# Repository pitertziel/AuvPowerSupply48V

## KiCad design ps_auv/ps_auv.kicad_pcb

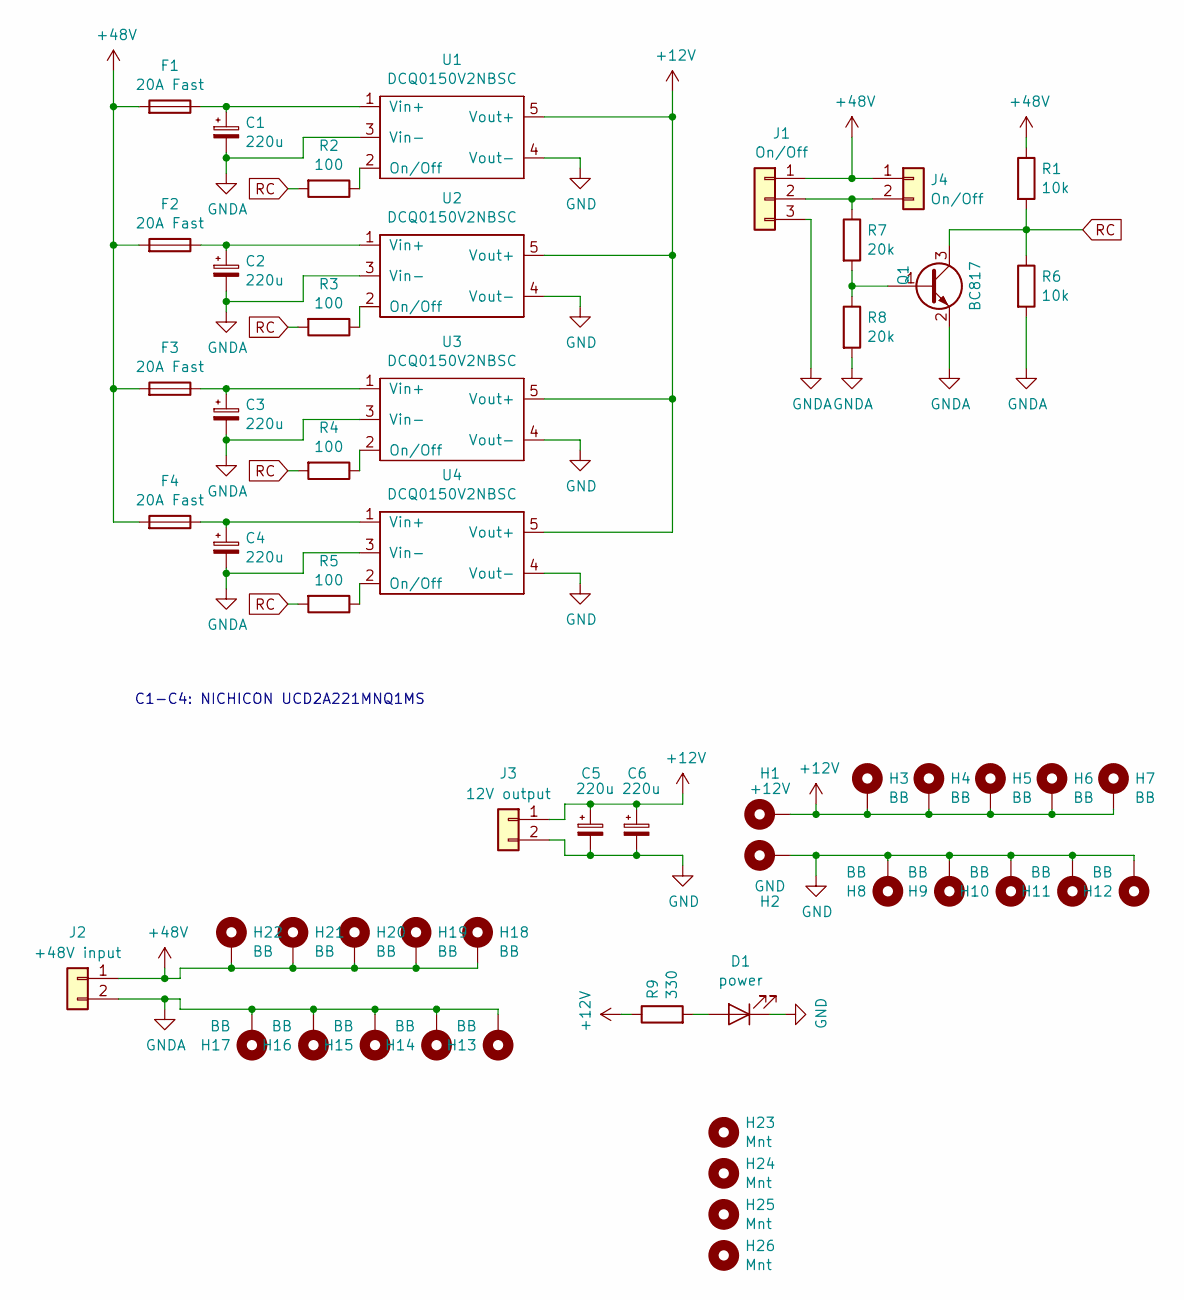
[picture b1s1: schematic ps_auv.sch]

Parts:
C1, C2, C3, C4: 220u; CP_Elec_18x17.5
C5, C6: 220u; CP_EIA-7343-43_Kemet-X
D1: power; LED_0805_2012Metric
F1, F2, F3, F4: 20A Fast; Fuseholder_Blade_Mini_Keystone_3568
H1: +12V; MountingHole_6.4mm_M6_Pad
H2: GND; MountingHole_6.4mm_M6_Pad
H3, H4, H5, H6, H7, H8, H9, H10, H11, H12, H13, H14, H15, H16, H17, H18, H19, H20, H21, H22: BB; MountingHole_2.2mm_M2_Pad
H23, H24, H25, H26: Mnt; MountingHole_2.2mm_M2
J1: On/Off; Molex_SPOX_5268-03A_1x03_P2.50mm_Horizontal
J2: +48V input
J3: 12V output
J4: On/Off; Molex_SPOX_5268-02A_1x02_P2.50mm_Horizontal
Q1: BC817; SOT-23
R1, R6: 10k; R_0805_2012Metric
R2, R3, R4, R5: 100; R_0805_2012Metric
R7, R8: 20k; R_0805_2012Metric
R9: 330; R_0805_2012Metric
U1, U2, U3, U4: DCQ0150V2NBSC; dcdc_48to12

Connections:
+12V: C5.1, C6.1, H1.1, H3.1, H4.1, H5.1, H6.1, H7.1, J3.1, R9.1, U1.5 (Vout+), U2.5 (Vout+), U3.5 (Vout+), U4.5 (Vout+)
+48V: F1.2, F2.2, F3.2, F4.2, H18.1, H19.1, H20.1, H21.1, H22.1, J1.1, J2.1, J4.1, R1.1
GND: C5.2, C6.2, D1.1 (K), H2.1, H8.1, H9.1, H10.1, H11.1, H12.1, J3.2, U1.4 (Vout-), U2.4 (Vout-), U3.4 (Vout-), U4.4 (Vout-)
GNDA: C1.2, C2.2, C3.2, C4.2, H13.1, H14.1, H15.1, H16.1, H17.1, J1.3, J2.2, Q1.2 (E), R6.2, R8.2, U1.3 (Vin-), U2.3 (Vin-), U3.3 (Vin-), U4.3 (Vin-)
unnamed: C1.1, F1.1, U1.1 (Vin+)
unnamed: C2.1, F2.1, U2.1 (Vin+)
unnamed: C3.1, F3.1, U3.1 (Vin+)
unnamed: C4.1, F4.1, U4.1 (Vin+)
unnamed: D1.2 (A), R9.2
unnamed: J1.2, J4.2, R7.1
unnamed: Q1.1 (B), R7.2, R8.1
unnamed: R2.1, U1.2 (On/Off)
unnamed: R3.1, U2.2 (On/Off)
unnamed: R4.1, U3.2 (On/Off)
unnamed: R5.1, U4.2 (On/Off)
RC: Q1.3 (C), R1.2, R2.2, R3.2, R4.2, R5.2, R6.1

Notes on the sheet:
C1-C4: NICHICON UCD2A221MNQ1MS

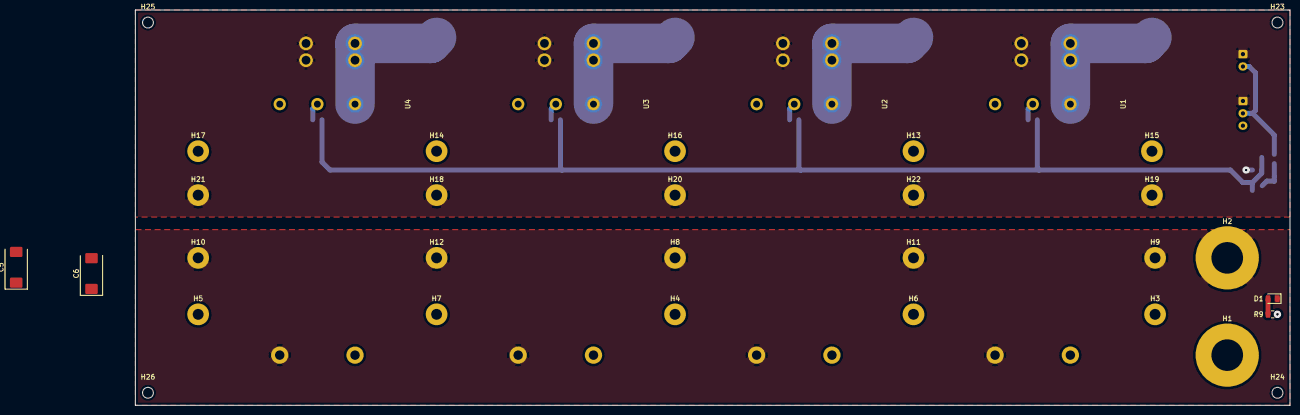
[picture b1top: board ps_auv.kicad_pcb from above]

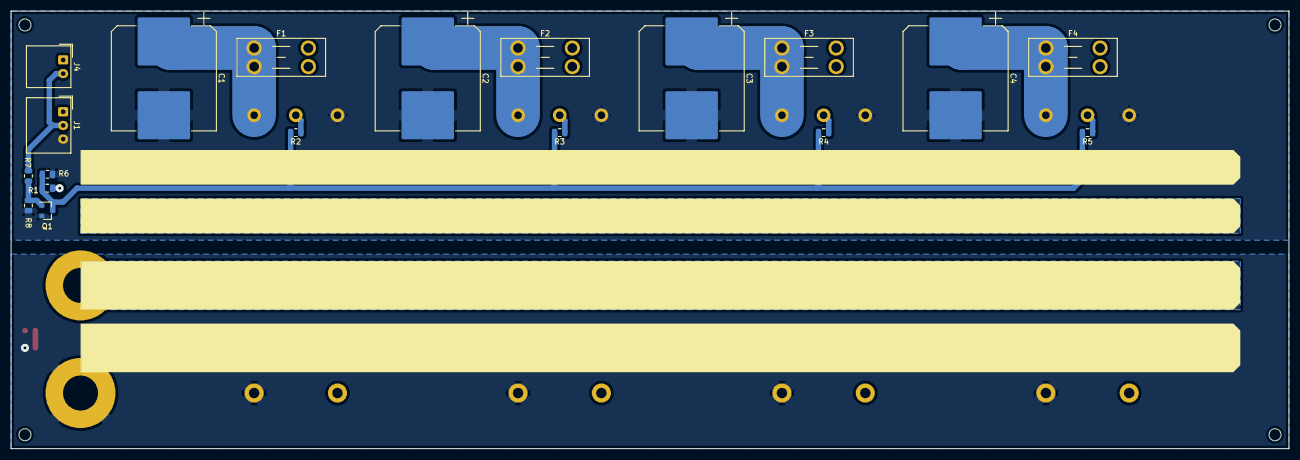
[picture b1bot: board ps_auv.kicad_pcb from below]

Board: 2 copper layers, 233.7 x 80.0 mm, 53 parts (19 on the bottom side), 16 nets.

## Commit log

2020-03-08 PSU 0.9.0
